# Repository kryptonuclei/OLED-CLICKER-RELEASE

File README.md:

# OLED-Clicker

This creation is designed to both be a fidget item while also being able to serve a purpose. It is an electronic counter and a fidget clicker utilizing mechanical keyboard switches. The OLED used is 1.3in across, larger than the typical horizontal OLEDs. The processor is an ATMEGA32U4, from an arduino leonardo framework. The code was developed in visual studio using arduino libraries. It is powered by an 18650 that is charged via a USB C connector. The 5V rail is connected to a TP4056 to handle the charging. The 32U4 is also connected to the USB C for programming.

A sleep mode is enabled after 1 minute of inactivity, during this mode, the clicker only draws 0.4mA, almost a year standby using a 3000mAh 18650!

There are some things that would be cool to integrate but have not been completed such as https://github.com/AlexIII/t-rex-duino and a selection of menus rather than the current mode toggles. The dino game has not yet been successfully integrated as it uses drivers which are written as part of the project, but this project uses an OLED that addresses with rows and columns swapped ie 64x128 rather than standard 128x64.

# Pictures

# Model

# PCB

# Components

Link to OLED: https://www.aliexpress.com/item/1648493376.html?spm=a2g0s.9042311.0.0.50434c4dDTX8kw

| Part  | Value                                   | Device                                  | Description                                                                                                                    |
| ----- | --------------------------------------- | --------------------------------------- | ------------------------------------------------------------------------------------------------------------------------------ |
| BT1   |                                         | BATTERY-18650-Holder                           | Battery - Single Cell                                                                                                          |
| C1    | 1u                                      | C-EUC0603                               | CAPACITOR, European symbol                                                                                                     |
| C2    | 100n                                    | C-EUC0603                               | CAPACITOR, European symbol                                                                                                     |
| C3    | 22p                                     | C-EUC0603                               | CAPACITOR, European symbol                                                                                                     |
| C4    | 22p                                     | C-EUC0603                               | CAPACITOR, European symbol                                                                                                     |
| C5    | 2.2u                                    | C-EUC0603                               | CAPACITOR, European symbol                                                                                                     |
| C6    | 0.1u                                    | C-EUC0603                               | CAPACITOR, European symbol                                                                                                     |
| C7    | 4.7u                                    | C-EUC0603                               | CAPACITOR, European symbol                                                                                                     |
| C8    | 0.1u                                    | C-EUC0603                               | CAPACITOR, European symbol                                                                                                     |
| C9    | 4.7u                                    | C-EUC0603                               | CAPACITOR, European symbol                                                                                                     |
| C10   | 10u                                     | C-EUC0805                               | CAPACITOR, European symbol                                                                                                     |
| C11   | 0.1u                                    | C-EUC0603                               | CAPACITOR, European symbol                                                                                                     |
| C12   | 0.1u                                    | C-EUC0603                               | CAPACITOR, European symbol                                                                                                     |
| C13   | 4.7p                                    | C-EUC0603                               | CAPACITOR, European symbol                                                                                                     |
| C14   | 0.1u                                    | C-EUC0603                               | CAPACITOR, European symbol                                                                                                     |
| D1    |                                         | LED0603                                 | LED (Generic)                                                                                                                  |
| D2    |                                         | LED0603                                 | LED (Generic)                                                                                                                  |
| D4    |                                         | LED0603                                 | LED (Generic)                                                                                                                  |
| D5    |                                         | LED0603                                 | LED (Generic)                                                                                                                  |
| D6    |                                         | DIODE\_SOD-123FL                        | Diode                                                                                                                          |
| IC1   | DW01A                                   | DW01A                                   | Battery Protection                                                                                                                               |
| IC2   | TP4056                                  | TP4056                                  | Battery Charger                                                                                                                               |
| J1    | DX07S016JA1R1500                        | DX07S016JA1R1500                        | USB-C (USB TYPE-C) USB 2.0 Receptacle Connector 24 (16+8 Dummy) Position Surface Mount, Right Angle; Through Hole  |
| L1    |                                         | L-EUL3225M                              | INDUCTOR, European symbol                                                                                                      |
| OLED1 | ADAFRUIT\_DISPLAY\_OLED\_128X64\_SH1107 | ADAFRUIT\_DISPLAY\_OLED\_128X64\_SH1107 | Horizontal ribbon 1.3in OLED                                                                                                   |
| Q1    | FS8205A                                 | FS8205A                                 | MOSFET                                                                                                                         |
| R1    | 22                                      | R-EU\_R0603                             | RESISTOR, European symbol                                                                                                      |
| R2    | 22                                      | R-EU\_R0603                             | RESISTOR, European symbol                                                                                                      |
| R3    | 10k                                     | R-EU\_R0603                             | RESISTOR, European symbol                                                                                                      |
| R4    | 330                                     | R-EU\_R0603                             | RESISTOR, European symbol                                                                                                      |
| R5    | 330                                     | R-EU\_R0603                             | RESISTOR, European symbol                                                                                                      |
| R6    | 560k                                    | R-EU\_R0603                             | RESISTOR, European symbol                                                                                                      |
| R7    | 4.7k                                    | R-EU\_R0603                             | RESISTOR, European symbol                                                                                                      |
| R8    | 1k                                      | R-EU\_R0603                             | RESISTOR, European symbol                                                                                                      |
| R9    | 1k                                      | R-EU\_R0603                             | RESISTOR, European symbol                                                                                                      |
| R10   | 1k                                      | R-EU\_R0603                             | RESISTOR, European symbol                                                                                                      |
| R11   | 1k                                      | R-EU\_R0603                             | RESISTOR, European symbol                                                                                                      |
| R12   | 100                                     | R-EU\_R0603                             | RESISTOR, European symbol                                                                                                      |
| R13   | 4.7k                                    | R-EU\_R0603                             | RESISTOR, European symbol                                                                                                      |
| R14   | 4.7k                                    | R-EU\_R0603                             | RESISTOR, European symbol                                                                                                      |
| R15   | 1.43m                                   | R-EU\_R0603                             | RESISTOR, European symbol                                                                                                      |
| R16   | 205k                                    | R-EU\_R0603                             | RESISTOR, European symbol                                                                                                      |
| U$1   | ATMEGA32U4QFN2                          | ATMEGA32U4QFN2                          | Atmel 44-pin 8-bit Microcontroller with 32KBytes of ISP Flash and USB Controller -----                                         |
| U$2   | CHERRY-MX                               | CHERRY-MX                               | Cherry MX series keyswitch                                                                                                     |
| U1    | TPS61040DBVR                            | TPS61040DBVR                            | Boost IC                                                                                                            |
| Y1    | 16MHz                                   | CRYSTAL-16MHZSMD-5X3.2                  | 16MHz Crystal                                                                                                                  |

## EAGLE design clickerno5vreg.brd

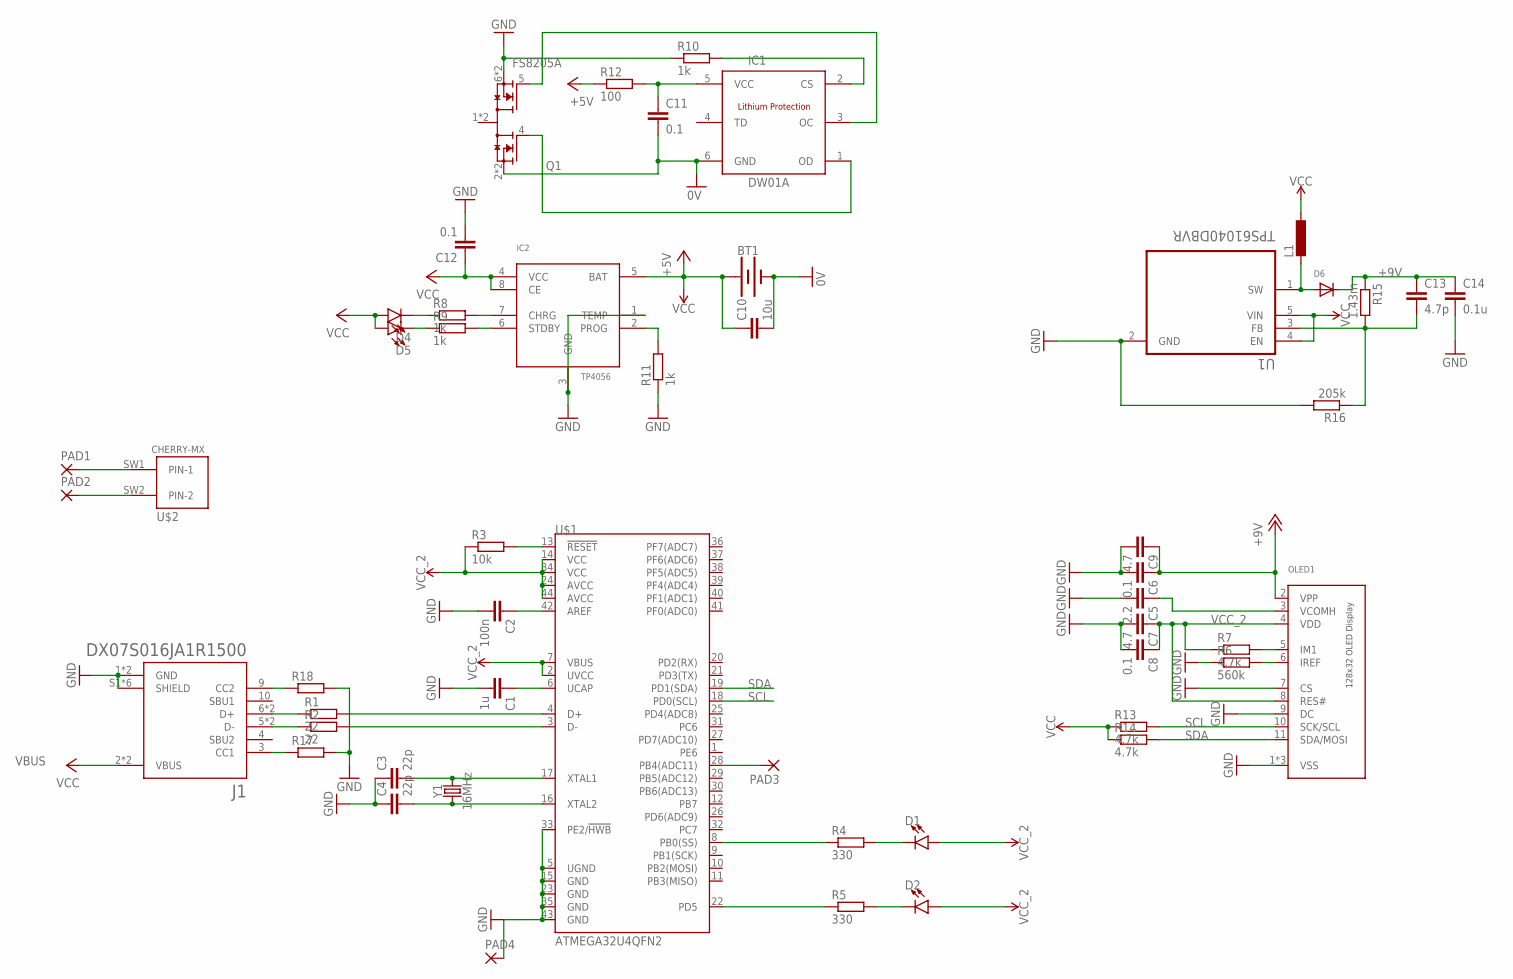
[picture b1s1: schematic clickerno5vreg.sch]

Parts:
BT1: BATTERY-18650; BATTERY_18650-HOLDER
C1: 1u; C0603
C2: 100n; C0603
C3, C4: 22p; C0603
C5: 2.2; C0603
C6, C8, C11, C12: 0.1; C0603
C7, C9: 4.7; C0603
C10: 10u; C0805
C13: 4.7p; C0603
C14: 0.1u; C0603
D1, D2, D4, D5: LED0603; LED-0603
D6: DIODE_SOD-123FL; SOD-123FL
IC1: DW01A; SOT23-6
IC2: TP4056; SOP-8
J1: DX07S016JA1R1500; JAE_DX07S016JA1R1500
L1: L-EUL3225M; L3225M
OLED1: ADAFRUIT_DISPLAY_OLED_128X64_SH1107; ADAFRUIT_DISPLAY_QT1107P11A
PAD1, PAD2, PAD3, PAD4: SMD5; SMD2,54-5,08
Q1: FS8205A; SOP65P640X120-8N
R1, R2: 22; R0603
R3: 10k; R0603
R4, R5: 330; R0603
R6: 560k; R0603
R7, R13, R14: 4.7k; R0603
R8, R9, R10, R11: 1k; R0603
R12: 100; R0603
R15: 1.43m; R0603
R16: 205k; R0603
R17, R18: R-EU_R0603; R0603
U1: TPS61040DBVR; SOT95P280X145-5N
U$1: ATMEGA32U4QFN2; SPARKFUN-DIGITALIC_QFN-44-NOPAD
U$2: CHERRY-MX
Y1: 16MHz; CRYSTAL-SMD-5X3.2-4PAD

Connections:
0V: BT1.GND@1 (-), C10.2, C11.2, IC1.6 (GND), Q1.2 (2,3), Q1.3 (2,3)
+9V: C6.1, C9.1, C13.1, C14.1, D6.C, OLED1.2 (VPP), R15.1
GND: C1.2, C2.2, C3.1, C4.1, C5.2, C6.2, C7.2, C8.2, C9.2, C12.2, C14.2, IC2.1 (TEMP), IC2.3 (GND), J1.1 (GND), J1.12 (GND), J1.S1 (SHIELD), J1.S2 (SHIELD), J1.S3 (SHIELD), J1.S4 (SHIELD), J1.S5 (SHIELD), J1.S6 (SHIELD), OLED1.1 (VSS), OLED1.7 (CS), OLED1.9 (DC), OLED1.12 (VSS), OLED1.13 (VSS), PAD4.1, Q1.6 (6,7), Q1.7 (6,7), R6.1, R10.1, R11.1, R16.2, R17.2, R18.2, U1.2 (GND), U$1.5 (UGND), U$1.15 (GND), U$1.23 (GND), U$1.33 (PE2/!HWB), U$1.35 (GND), U$1.43 (GND)
unnamed: C1.1, U$1.6 (UCAP)
unnamed: C2.1, U$1.42 (AREF)
unnamed: J1.6 (D+), J1.8 (D+), R1.1
unnamed: J1.5 (D-), J1.7 (D-), R2.1
unnamed: R1.2, U$1.4 (D+)
unnamed: R2.2, U$1.3 (D-)
unnamed: C4.2, U$1.16 (XTAL2), Y1.1
unnamed: C3.2, U$1.17 (XTAL1), Y1.3 (2)
unnamed: IC2.6 (STDBY), R9.2
unnamed: R3.2, U$1.13 (!RESET)
unnamed: R5.1, U$1.22 (PD5)
unnamed: R4.1, U$1.8 (PB0(SS))
unnamed: D1.C, R4.2
unnamed: D2.C, R5.2
unnamed: C5.1, OLED1.3 (VCOMH)
unnamed: C13.2, R15.2, R16.1, U1.3 (FB)
unnamed: OLED1.5 (IM1), R7.2
unnamed: IC1.1 (OD), Q1.4
unnamed: OLED1.6 (IREF), R6.2
unnamed: IC2.7 (CHRG), R8.2
unnamed: IC1.3 (OC), Q1.5
unnamed: C11.1, IC1.5 (VCC), R12.2
unnamed: D5.C, R9.1
unnamed: D4.C, R8.1
unnamed: IC2.2 (PROG), R11.2
unnamed: IC1.2 (CS), R10.2
unnamed: D6.A, L1.2, U1.1 (SW)
unnamed: PAD3.1, U$1.28 (PB4(ADC11))
unnamed: PAD2.1, U$2.SW2 (PIN-2)
unnamed: PAD1.1, U$2.SW1 (PIN-1)
unnamed: J1.3 (CC1), R17.1
unnamed: J1.9 (CC2), R18.1
SCL: OLED1.10 (SCK/SCL), R13.2, U$1.18 (PD0(SCL))
SDA: OLED1.11 (SDA/MOSI), R14.2, U$1.19 (PD1(SDA))
VBUS: C12.1, D4.A, D5.A, IC2.4 (VCC), IC2.8 (CE), J1.2 (VBUS), J1.11 (VBUS)
VCC_2: BT1.PWR@1 (+), C7.1, C8.1, C10.1, D1.A, D2.A, IC2.5 (BAT), L1.1, OLED1.4 (VDD), OLED1.8 (RES#), R3.1, R7.1, R12.1, R13.1, R14.1, U1.4 (EN), U1.5 (VIN), U$1.2 (UVCC), U$1.7 (VBUS), U$1.14 (VCC), U$1.24 (AVCC), U$1.34 (VCC), U$1.44 (AVCC)

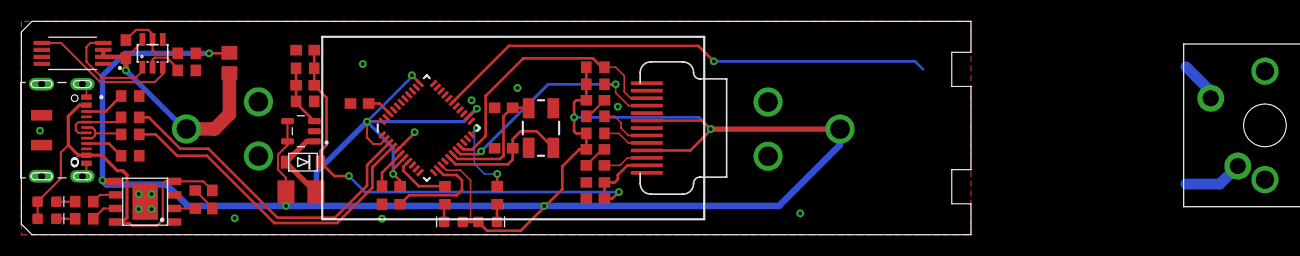
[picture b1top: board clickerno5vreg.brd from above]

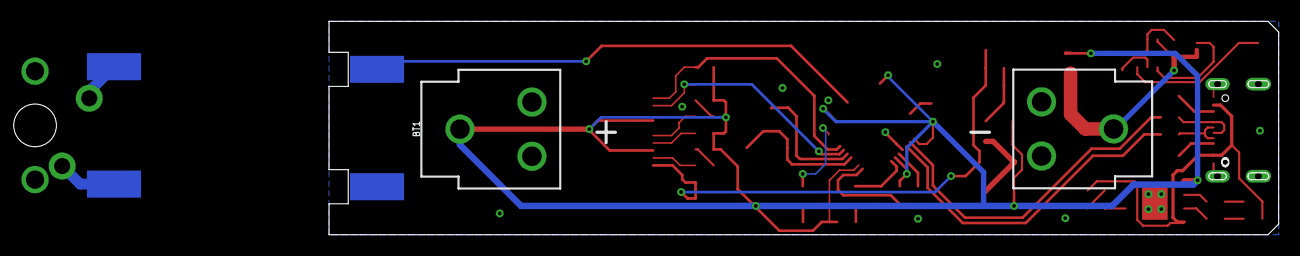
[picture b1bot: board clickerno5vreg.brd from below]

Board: 2 copper layers, 89.0 x 20.0 mm, 52 parts (5 on the bottom side), 39 nets.

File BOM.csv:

"Part","Value","Device","Package","Description","",
"BT1","","BATTERY-18650","BATTERY_18650-HOLDER","Battery - Single Cell","",
"C1","1u","C-EUC0603","C0603","CAPACITOR, European symbol","",
"C2","100n","C-EUC0603","C0603","CAPACITOR, European symbol","",
"C3","22p","C-EUC0603","C0603","CAPACITOR, European symbol","",
"C4","22p","C-EUC0603","C0603","CAPACITOR, European symbol","",
"C5","2.2","C-EUC0603","C0603","CAPACITOR, European symbol","",
"C6","0.1","C-EUC0603","C0603","CAPACITOR, European symbol","",
"C7","4.7","C-EUC0603","C0603","CAPACITOR, European symbol","",
"C8","0.1","C-EUC0603","C0603","CAPACITOR, European symbol","",
"C9","4.7","C-EUC0603","C0603","CAPACITOR, European symbol","",
"C10","10u","C-EUC0805","C0805","CAPACITOR, European symbol","",
"C11","0.1","C-EUC0603","C0603","CAPACITOR, European symbol","",
"C12","0.1","C-EUC0603","C0603","CAPACITOR, European symbol","",
"C13","4.7p","C-EUC0603","C0603","CAPACITOR, European symbol","",
"C14","0.1u","C-EUC0603","C0603","CAPACITOR, European symbol","",
"D1","","LED0603","LED-0603","LED (Generic)","",
"D2","","LED0603","LED-0603","LED (Generic)","",
"D4","","LED0603","LED-0603","LED (Generic)","",
"D5","","LED0603","LED-0603","LED (Generic)","",
"D6","","DIODE_SOD-123FL","SOD-123FL","Diode","",
"IC1","DW01A","DW01A","SOT23-6","","",
"IC2","TP4056","TP4056","SOP-8","","",
"J1","DX07S016JA1R1500","DX07S016JA1R1500","JAE_DX07S016JA1R1500","USB-C (USB TYPE-C) USB 2.0 Receptacle Connector 24 (16+8 Dummy) Position Surface Mount, Right Angle; Through Hole Check prices","",
"L1","","L-EUL3225M","L3225M","INDUCTOR, European symbol","",
"OLED1","ADAFRUIT_DISPLAY_OLED_128X64_SH1107","ADAFRUIT_DISPLAY_OLED_128X64_SH1107","ADAFRUIT_DISPLAY_QT1107P11A","","",
"PAD1","","SMD5","SMD2,54-5,08","SMD PAD","",
"PAD2","","SMD5","SMD2,54-5,08","SMD PAD","",
"PAD3","","SMD5","SMD2,54-5,08","SMD PAD","",
"PAD4","","SMD5","SMD2,54-5,08","SMD PAD","",
"Q1","FS8205A","FS8205A","SOP65P640X120-8N","N/A","",
"R1","22","R-EU_R0603","R0603","RESISTOR, European symbol","",
"R2","22","R-EU_R0603","R0603","RESISTOR, European symbol","",
"R3","10k","R-EU_R0603","R0603","RESISTOR, European symbol","",
"R4","330","R-EU_R0603","R0603","RESISTOR, European symbol","",
"R5","330","R-EU_R0603","R0603","RESISTOR, European symbol","",
"R6","560k","R-EU_R0603","R0603","RESISTOR, European symbol","",
"R7","4.7k","R-EU_R0603","R0603","RESISTOR, European symbol","",
"R8","1k","R-EU_R0603","R0603","RESISTOR, European symbol","",
"R9","1k","R-EU_R0603","R0603","RESISTOR, European symbol","",
"R10","1k","R-EU_R0603","R0603","RESISTOR, European symbol","",
"R11","1k","R-EU_R0603","R0603","RESISTOR, European symbol","",
"R12","100","R-EU_R0603","R0603","RESISTOR, European symbol","",
"R13","4.7k","R-EU_R0603","R0603","RESISTOR, European symbol","",
"R14","4.7k","R-EU_R0603","R0603","RESISTOR, European symbol","",
"R15","1.43m","R-EU_R0603","R0603","RESISTOR, European symbol","",
"R16","205k","R-EU_R0603","R0603","RESISTOR, European symbol","",
"U$1","ATMEGA32U4QFN2","ATMEGA32U4QFN2","SPARKFUN-DIGITALIC_QFN-44-NOPAD","Atmel 44-pin 8-bit Microcontroller with 32KBytes of ISP Flash and USB Controller -----","",
"U$2","CHERRY-MX","CHERRY-MX","CHERRY-MX","Cherry MX series keyswitch","",
"U1","TPS61040DBVR","TPS61040DBVR","SOT95P280X145-5N","Check prices","",
"Y1","16MHz","CRYSTAL-16MHZSMD-5X3.2","CRYSTAL-SMD-5X3.2-4PAD","16MHz Crystal","",

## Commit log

2021-10-08 added pd resistors

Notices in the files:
parts and their libraries:
SparkFun-Batteries: Licensing: Creative Commons ShareAlike 4.0 International - https://creativecommons.org/licenses/by-sa/4.0
